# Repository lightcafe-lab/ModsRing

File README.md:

# ModsRing
ModsRingは**smdMod**を使用したモジュール式のスマートリングです<br>
**smdMod** = **S**urface **M**ount **D**evice **Mod**ule（表面実装式の基板モジュール）の略称です<br><br>
LIGHTCAFE LAB ModsRing 作品ページ<br>
https://lab.lightcafe.co.jp/work/modsring<br>
LIGHTCAFE LAB smdMod 作品ページ<br>
https://lab.lightcafe.co.jp/work/smdmod<br>

## firmware
ModsRingに書き込むArduinoのサンプルスケッチです<br>

*ble-finger-mouse*<br>
PCとBluetooth接続すると指マウスになります<br>
## hardware
ModsRing付属のハードウェアです<br>

*modsring.stl*<br>
リング形状のカバーです。22号リング(内径:20ｍｍ)のサイズになっています<br>
市販の3Dプリンタで作成できます<br>

## smdMod
KiCad (v6.0.10)を使用した回路図と基板図です<br>

*base-board/mr-base*<br>
ModsRingのベース基板です<br>

*modules/mcu-and-power*<br>
MCUと電源モジュール<br>
・MCUモジュール：ISP1807(nRF52840）をBGAピッチ（1.00mmピッチ、Φ0.6mm）に変換<br>
・電源モジュール1：3.3Vレギュレータ+LiPo充電+LiPo/USB電源切替<br>
・電源モジュール2：LiPoバッテリゲージ+LiPo電池接続パッド<br>

*modules/switch-led-and-accel-sensor*<br>
GPIOとセンサモジュール<br>
・拡張モジュール1（フルカラーLED＋スイッチ）<br>
・拡張モジュール2（加速度センサ）<br>

*modules/usb-interface*<br>
USB I/F用の基板<br>
・基板1（USB-C）<br>
・基板2（USBピン）<br>

*options/127to254-pitch-convert*<br>
モジュールのピッチ変換基板<br>
・1.27mmピッチ_10ピンを2.54mmピッチ_10ピンに変換します<br>

## ライセンスについて
この 作品 は <a rel="license" href="https://creativecommons.org/licenses/by-sa/4.0/deed.ja">クリエイティブ・コモンズ 表示 - 継承 4.0 国際 ライセンス</a>の下に提供されています<br>
<br />

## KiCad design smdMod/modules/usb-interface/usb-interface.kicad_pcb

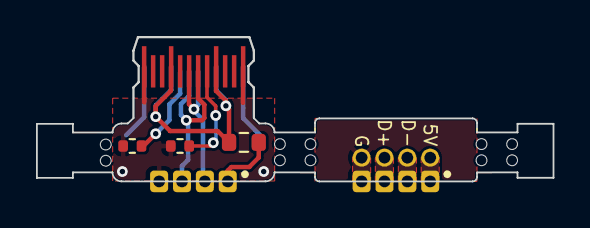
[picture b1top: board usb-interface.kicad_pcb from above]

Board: 2 copper layers, 28.7 x 8.0 mm, 6 parts (1 on the bottom side), 7 nets.

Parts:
CN1: CON_USB-CPCBPLUG; USB-C_PCBPLUG
J1: Conn_01x04; pad_1x04_P1.27mm_usbc
J2: Conn_01x04; pad_1x04_P1.27mm_usbc_with_hole
PL1: 0ZCM0003FF2G; R_0603_1608Metric
R3, R4: 5.1k; R_0402_1005Metric_nosilk

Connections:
+5V: J1.1, PL1.2
/USBD+: CN1.P$A6 (D+1), CN1.P$B6 (D+2), J1.3
/USBD-: CN1.P$A7 (D-1), CN1.P$B7 (D-2), J1.2
GNDA: CN1.P$A1 (GND1), CN1.P$A12 (GND2), CN1.P$B1 (GND3), CN1.P$B12 (GND4), J1.4, R3.2, R4.2
unnamed: CN1.P$A5 (CC1), R3.1
unnamed: CN1.P$B5 (CC2), R4.1
VBUS: CN1.P$A4 (VBUS1), CN1.P$A9 (VBUS2), CN1.P$B4 (VBUS3), CN1.P$B9 (VBUS4), PL1.1

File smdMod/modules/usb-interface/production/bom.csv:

Designator,Footprint,Quantity,Value,LCSC Part #
CN1,USB-C_PCBPLUG,1,CON_USB-CPCBPLUG,
J1,pad_1x04_P1.27mm_usbc,1,Conn_01x04,
J2,pad_1x04_P1.27mm_usbc_with_hole,1,Conn_01x04,
PL1,0603,1,0ZCM0003FF2G,
"R3, R4",0402,2,5.1k,

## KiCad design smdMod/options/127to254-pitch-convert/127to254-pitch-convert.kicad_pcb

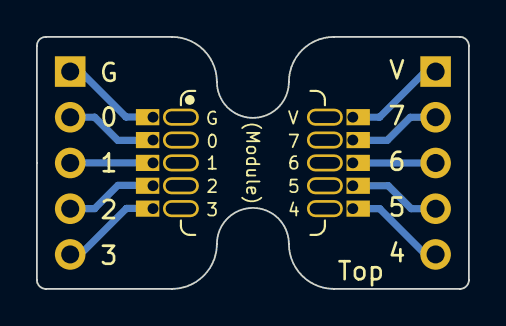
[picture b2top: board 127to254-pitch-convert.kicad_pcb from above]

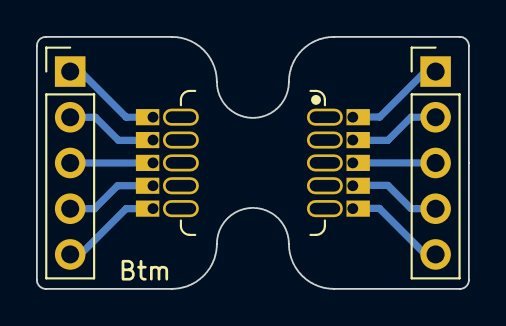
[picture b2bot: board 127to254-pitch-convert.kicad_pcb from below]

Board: 2 copper layers, 24.0 x 14.0 mm, 4 parts (2 on the bottom side), 10 nets.

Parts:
J1, J4: Conn_01x05_Male; PinHeader_1x05_P2.54mm_Vertical
J2: Conn_01x05_Female; FlexyPin_1x05_P1.27mm-with-line-L
J3: Conn_01x05_Female; FlexyPin_1x05_P1.27mm-with-line-R

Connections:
unnamed: J1.1, J2.1
unnamed: J1.2, J2.2
unnamed: J1.3, J2.3
unnamed: J1.4, J2.4
unnamed: J1.5, J2.5
unnamed: J3.1, J4.1
unnamed: J3.2, J4.2
unnamed: J3.3, J4.3
unnamed: J3.4, J4.4
unnamed: J3.5, J4.5

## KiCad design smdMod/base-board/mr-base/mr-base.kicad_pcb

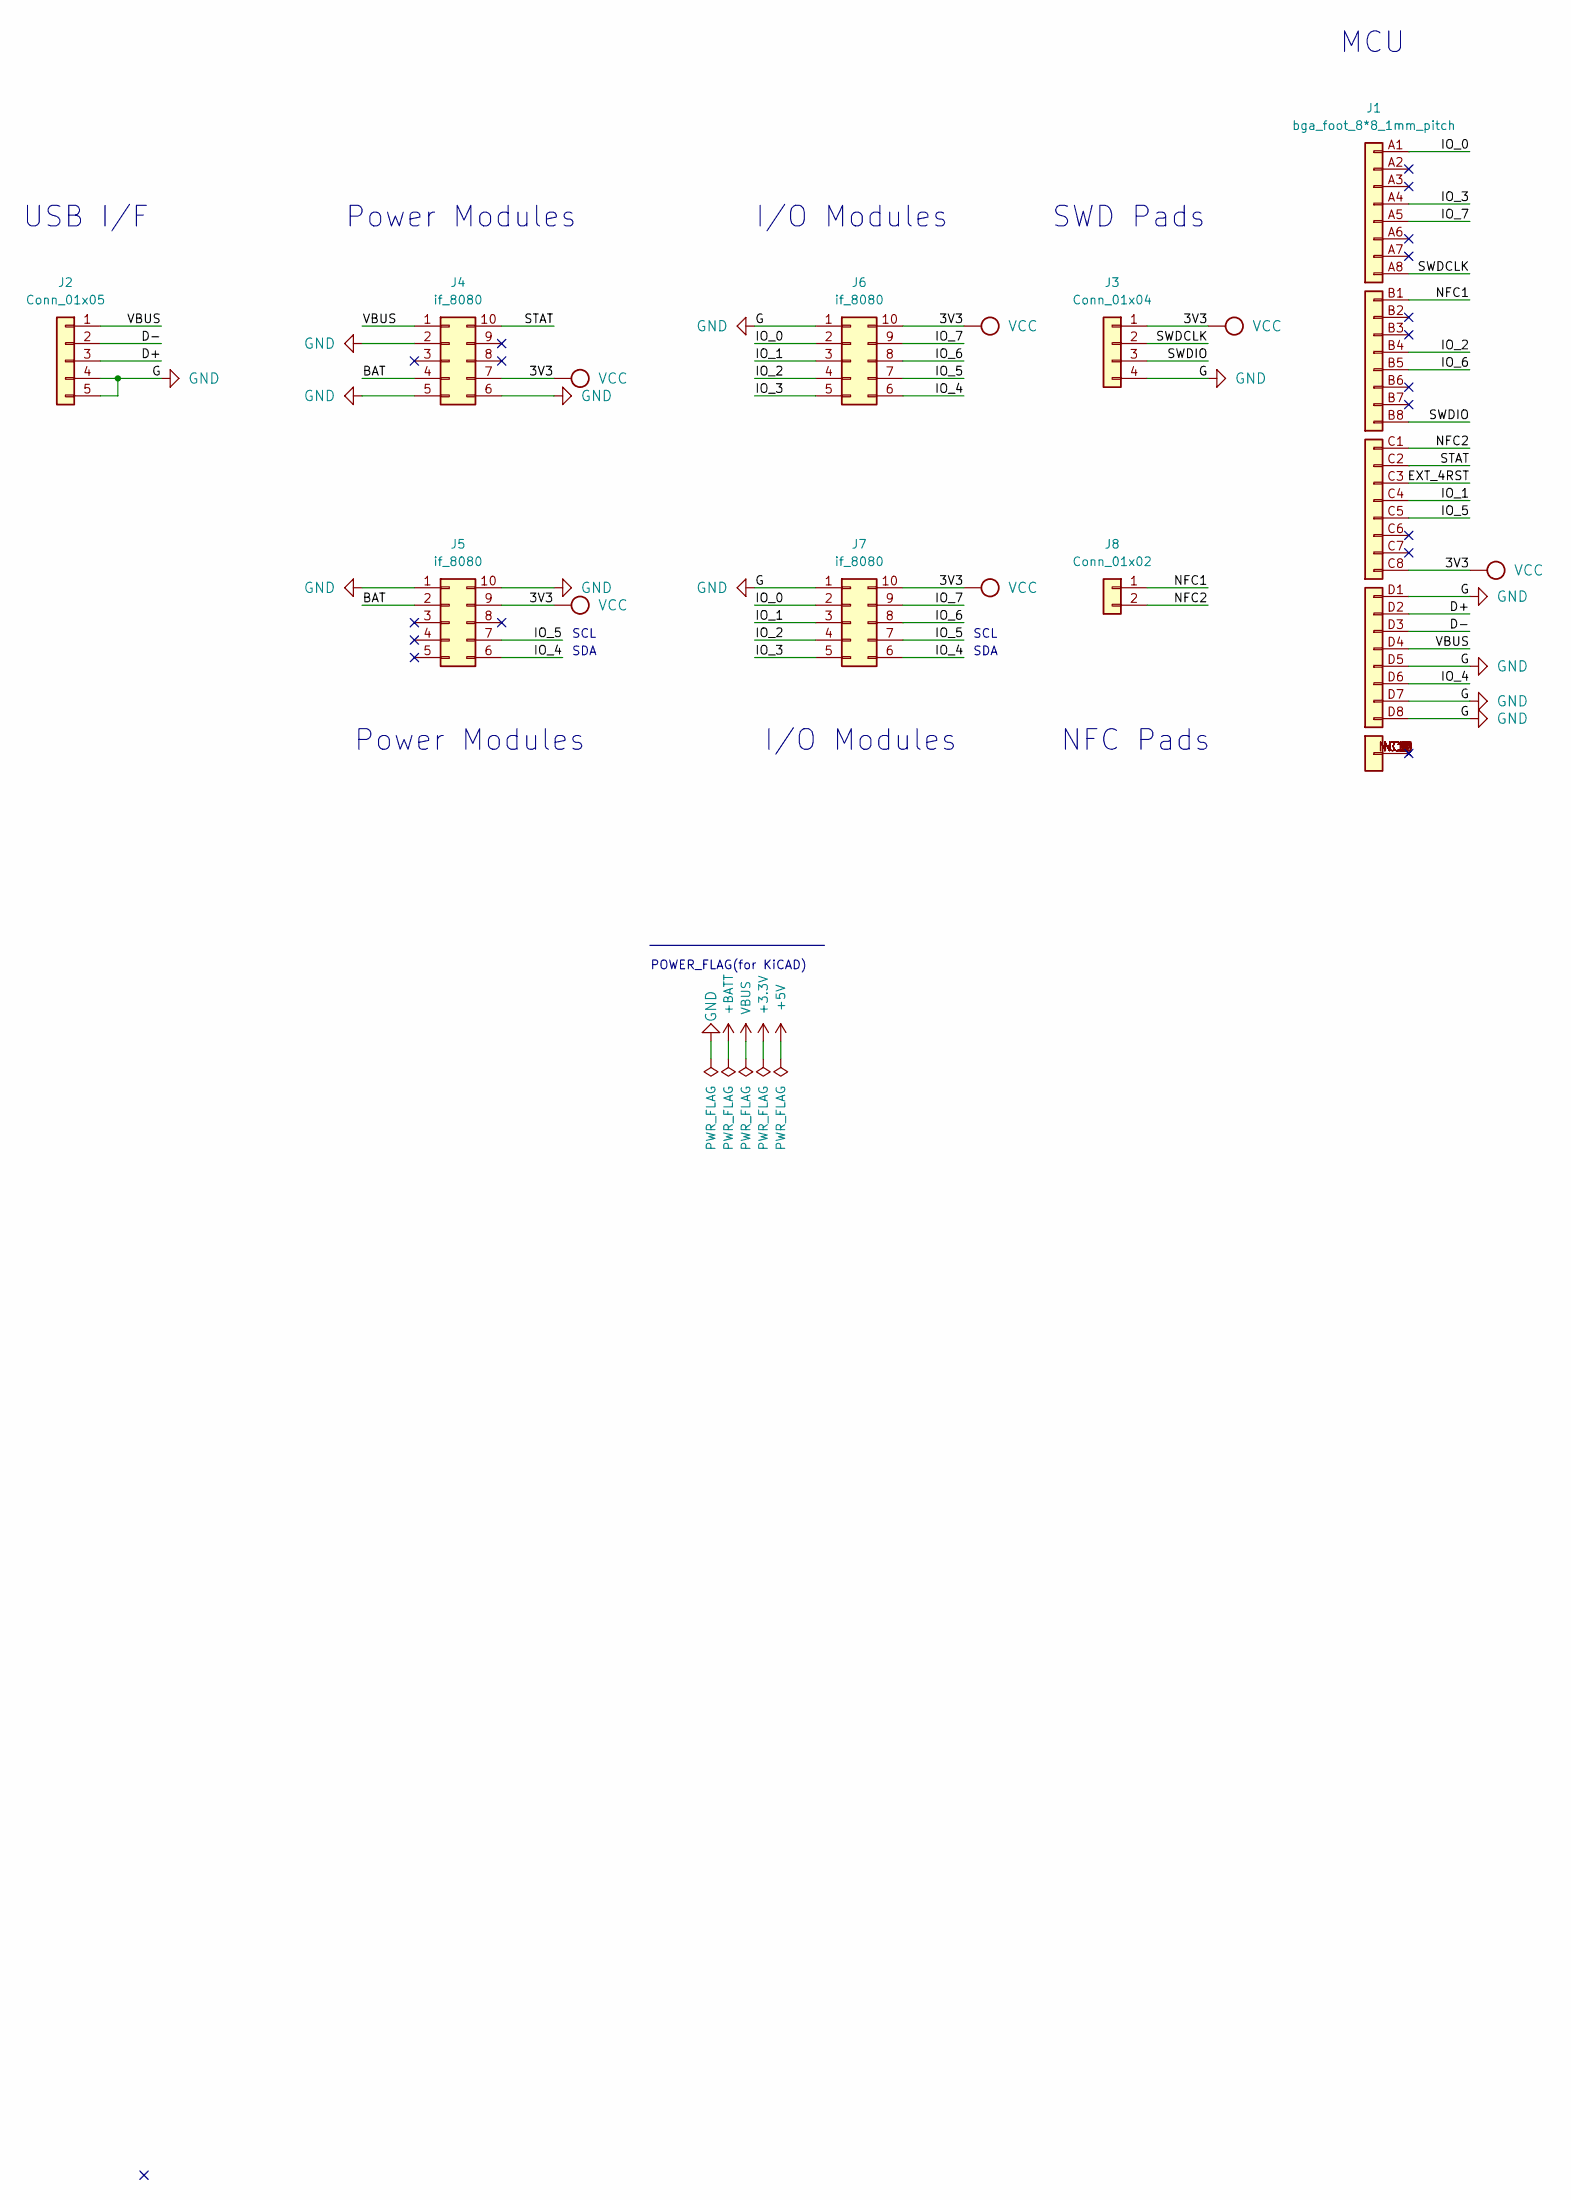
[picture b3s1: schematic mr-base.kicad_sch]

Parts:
J1: bga_foot_8*8_1mm_pitch; if-8080-mcu-v1-for-board
J2: Conn_01x05; pad_1x04_P1.27mm_usbc_mount
J3: Conn_01x04; pad_1x04_P1.27mm
J4, J5: if_8080; if-8080-10pin-mount-free-pin
J6, J7: if_8080; if-8080-10pin-mount-HAT
J8: Conn_01x02; pad_1x02_P1.27mm

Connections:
/BAT: J4.4, J5.2
/D+: J1.D2, J2.3
/D-: J1.D3, J2.2
/EXT_4RST: J1.C3
/IO_0: J1.A1, J6.2, J7.2
/IO_1: J1.C4, J6.3, J7.3
/IO_2: J1.B4, J6.4, J7.4
/IO_3: J1.A4, J6.5, J7.5
/IO_4: J1.D6, J5.6, J6.6, J7.6
/IO_5: J1.C5, J5.7, J6.7, J7.7
/IO_6: J1.B5, J6.8, J7.8
/IO_7: J1.A5, J6.9, J7.9
/NFC1: J1.B1, J8.1
/NFC2: J1.C1, J8.2
/STAT: J1.C2, J4.10
/SWDCLK: J1.A8, J3.2
/SWDIO: J1.B8, J3.3
GND: J1.D1, J1.D5, J1.D7, J1.D8, J2.4, J2.5, J3.4, J4.2, J4.5, J4.6, J5.1, J5.10, J6.1, J7.1
VBUS: J1.D4, J2.1, J4.1
VCC: J1.C8, J3.1, J4.7, J5.9, J6.10, J7.10

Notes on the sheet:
SWD Pads
USB I/F
SCL
I/O Modules
SDA
NFC Pads
POWER_FLAG(for KiCAD)
Power Modules
MCU

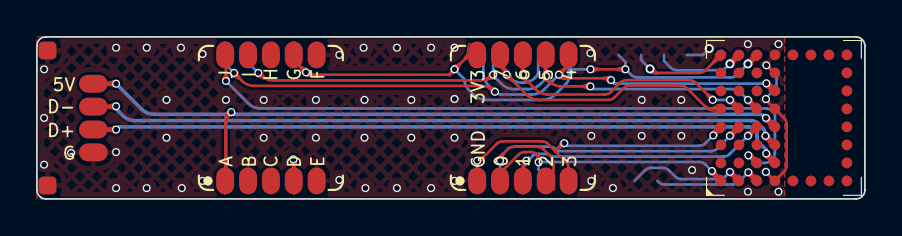
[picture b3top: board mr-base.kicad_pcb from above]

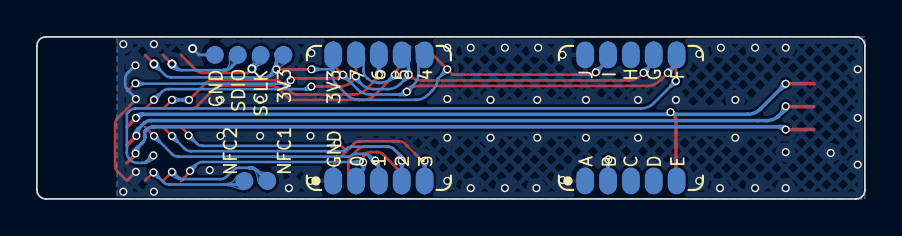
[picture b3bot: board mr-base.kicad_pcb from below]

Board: 2 copper layers, 46.0 x 9.0 mm, 8 parts (4 on the bottom side), 19 nets.

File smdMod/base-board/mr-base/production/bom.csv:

Designator,Footprint,Quantity,Value,LCSC Part #
J1,if-8080-mcu-v1-for-board,1,bga_foot_8*8_1mm_pitch,
J2,pad_1x04_P1.27mm_usbc_mount,1,Conn_01x05,
J3,pad_1x04_P1.27mm,1,Conn_01x04,
"J4, J5",if-8080-10pin-mount-free-pin,2,if_8080,
"J6, J7",if-8080-10pin-mount-HAT,2,if_8080,
J8,pad_1x02_P1.27mm,1,Conn_01x02,

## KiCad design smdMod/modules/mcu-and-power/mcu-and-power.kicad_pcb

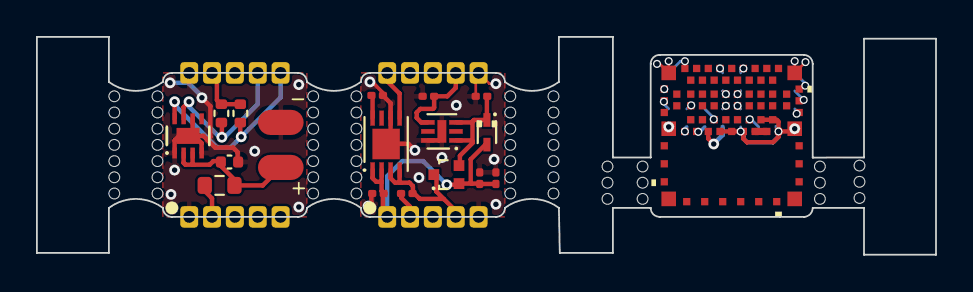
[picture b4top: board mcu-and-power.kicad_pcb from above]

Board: 2 copper layers, 49.9 x 12.1 mm, 21 parts (0 on the bottom side), 33 nets.

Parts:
C1: 0.1uF; C_0402_1005Metric_nosilk
C2, C3, C5, C6: 2.2uF; C_0201_0603Metric_nosilk
C4: 0.1uF; C_0201_0603Metric_nosilk
D1: NSR05T40XV2
IC1: MAX17048G; MAX17048G-L
IC2: MCP73832-2ACI-MC; MCP73832-2ACIMC
IC3: MIC5514-3.3YMT-TR
IC4: ISP1807-LR-RS
J1: Conn_01x02_Male; 1×02_pinhead_smd
J2, J3: if_8080; if-8080-10pin-castle-v1
J4: bga_foot_8*8_1mm_pitch; if-8080-mcu-v1
PL1: 0ZCM0003FF2G; R_0603_1608Metric
Q1: Q_PMOS_GSD; SSM3j36FS
R1, R2: 10k; R_0402_1005Metric_nosilk
R3: 18k; R_0201_0603Metric_nosilk
R4: 100k; R_0201_0603Metric_nosilk

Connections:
/3V3_A: J2.9, R1.2, R2.2
/3V3_B: C6.1, IC3.4 (VOUT), J3.7
/BAT_A: J2.2, PL1.2
/BAT_B: C3.1, IC2.3 (VBAT), IC2.4 (VBAT), J3.4, Q1.3 (D)
/D+: IC4.8 (D+), J4.D2
/D-: IC4.10 (D-), J4.D3
/EXT_4RST: IC4.13 (P0_18_RESET), J4.C3
/IO_0: IC4.48 (P0_28_AIN4), J4.A1
/IO_1: IC4.61 (P1_11), J4.C4
/IO_2: IC4.53 (P1_13), J4.B4
/IO_3: IC4.42 (P0_31_AIN7), J4.A4
/IO_4: IC4.19 (P0_24), J4.D6
/IO_5: IC4.60 (P1_10), J4.C5
/IO_6: IC4.52 (P1_14), J4.B5
/IO_7: IC4.38 (P0_03_AIN1), J4.A5
/LIPO_IN: C1.1, IC1.2 (CELL), IC1.3 (Vdd), J1.1, PL1.1
/NFC1: IC4.2 (P0_09_NFC1), J4.B1
/NFC2: IC4.4 (P0_10_NFC2), J4.C1
/SCL: IC1.7 (SCL), J2.7, R1.1
/SDA: IC1.8 (SDA), J2.6, R2.1
/STAT: IC4.64 (P1_01), J4.C2
/STAT_B: IC2.5 (STAT), J3.10
/SWDCLK: IC4.30 (SWDCLK), J4.A8
/SWDIO: IC4.28 (SWDIO), J4.B8
/USB5V: C2.1, C4.1, D1.2 (A), IC2.1 (VDD), IC2.2 (VDD), J3.1, Q1.1 (G), R4.2
GND: IC4.1 (VSS), IC4.7 (VSS), IC4.14 (VSS), IC4.16 (VSS), IC4.18 (VSS), IC4.21 (VSS), IC4.23 (VSS), IC4.24 (VSS), IC4.25 (VSS), IC4.31 (VSS), J4.D1, J4.D5, J4.D7, J4.D8
GNDA: C1.2, IC1.1 (CTG), IC1.4 (GND), IC1.6 (QSTRT), IC1.9 (EP), J1.2, J2.1, J2.10
GNDB: C2.2, C3.2, C4.2, C5.2, C6.2, IC2.6 (Vss), IC2.9 (EP), IC3.6 (GND), IC3.7 (EP), J3.2, J3.5, J3.6, R3.2, R4.1
unnamed: C5.1, D1.1 (K), IC3.1 (EN), IC3.3 (VIN), Q1.2 (S)
unnamed: IC2.8 (PROG), R3.1
unnamed: IC4.20 (OUT_ANT), IC4.22 (OUT_MOD)
VBUS: IC4.12 (VBUS), J4.D4
VCC: IC4.26 (VCC_NRF), J4.C8

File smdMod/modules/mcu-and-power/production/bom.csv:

Designator,Footprint,Quantity,Value,LCSC Part #
C1,402,1,0.1uF,
"C2, C3, C5, C6",201,4,2.2uF,
C4,201,1,0.1uF,
D1,NSR05T40XV2,1,NSR05T40XV2,
IC1,MAX17048G-L,1,MAX17048G,
IC2,MCP73832-2ACIMC,1,MCP73832-2ACI-MC,
IC3,MIC5514-3.3YMT-TR,1,MIC5514-3.3YMT-TR,
IC4,ISP1807-LR-RS,1,ISP1807-LR-RS,
PL1,603,1,0ZCM0003FF2G,
Q1,SSM3j36FS,1,Q_PMOS_GSD,
"R1, R2",402,2,10k,
R3,201,1,18k,
R4,201,1,100k,

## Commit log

2024-03-28 Create LICENSE
    add LICENSE CC BY-SA 4.0
